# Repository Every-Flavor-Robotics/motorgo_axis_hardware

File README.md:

# MotorGo AXIS
## The aim of this project is to integrate a dual bldc motor controller with an ESP32 AND make it piHat compatible for the rpi 4 and 5
### Schematics and Layouts and Renders: 
(This is a first pass draft, so be patient with my formatting and content)

- Full board 3D:

- Top level

- Motor drivers 

- IMU 

- Power system 

- connectors 

- Dimensions 

## Demo
This is still in testing, but already at this state, it is capable of making 2 axis gantry robots quite easily.  Check out this project we made with it while developing the motor controller:
https://www.youtube.com/watch?v=p4cUWCG7fM4

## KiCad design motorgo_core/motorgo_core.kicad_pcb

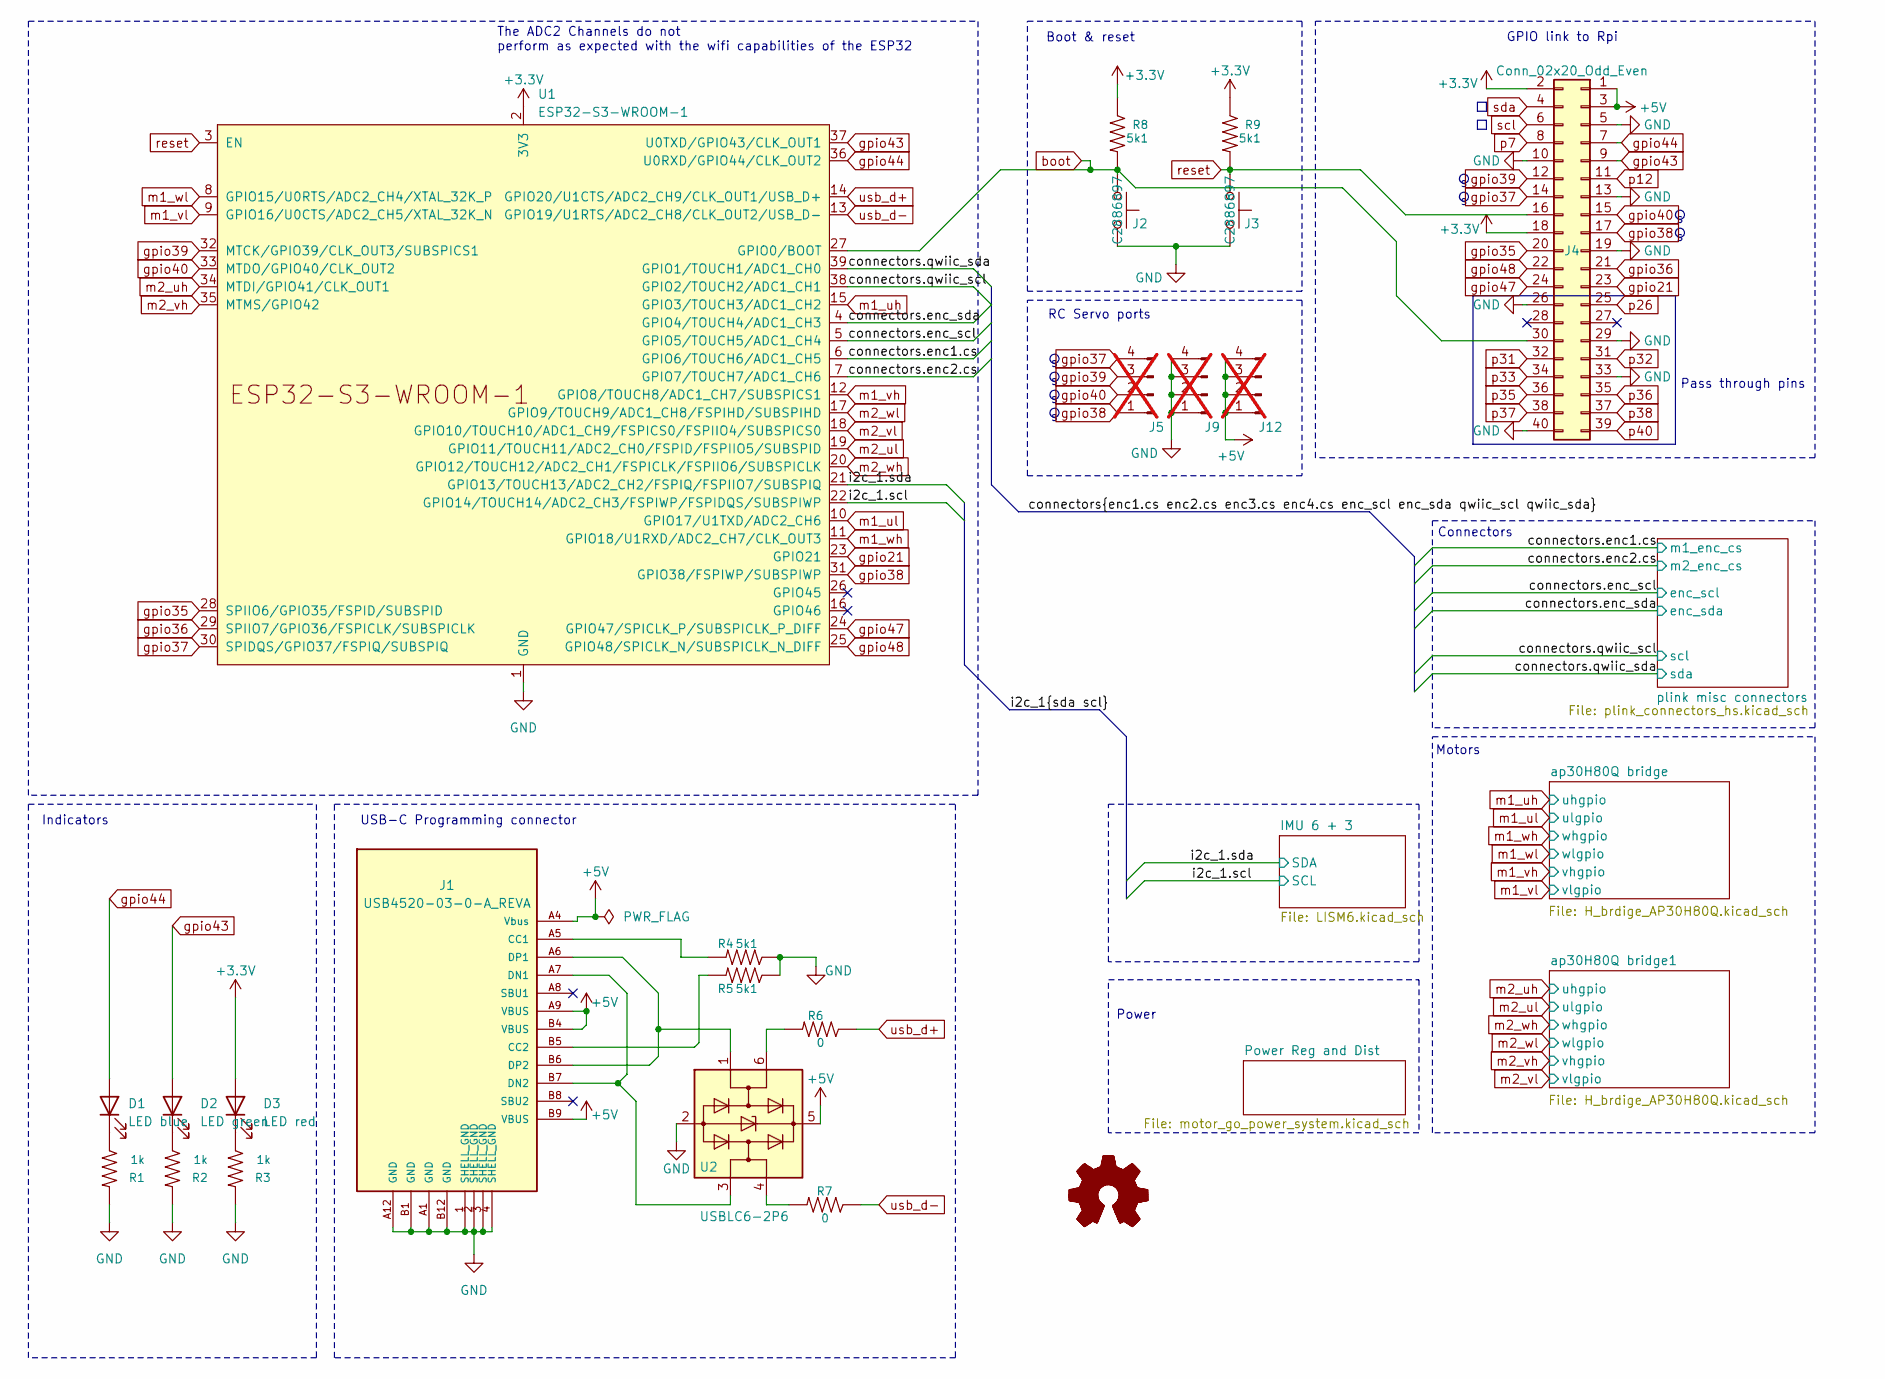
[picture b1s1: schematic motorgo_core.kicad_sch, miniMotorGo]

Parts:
D1: LED blue; LED_0805_2012Metric; LCSC_Part_Number C84259
D2: LED green; LED_0805_2012Metric; LCSC_Part_Number C84260
D3: LED red; LED_0805_2012Metric; LCSC_Part_Number C84256
J1: USB4520-03-0-A_REVA; USB-C-SMD_TYPEC-303-ACP16; LCSC_Part_Number C720628
J2, J3: C2886897; SW_SPST_TL3342; LCSC_Part_Number C2886897
J4: Conn_02x20_Odd_Even; PinSocket_2x20_P2.54mm_Vertical_SMD; LCSC_Part_Number C3975165
J5, J9, J12: Conn_01x04_Pin; PinHeader_1x04_P2.54mm_Vertical; not fitted
R1, R2, R3: 1k; R_0402_1005Metric; LCSC_Part_Number C11702
R4, R5, R8, R9: 5k1; R_0402_1005Metric; LCSC_Part_Number C25905
R6, R7: 0; R_0402_1005Metric; LCSC_Part_Number C3017451
U1: ESP32-S3-WROOM-1; LCSC_Part_Number C2913198
U2: USBLC6-2P6; SOT-666; LCSC_Part_Number C2827693

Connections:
+3.3V: D3.2 (A), J4.2, J4.18, R8.1, R9.1, U1.2 (3V3); also elsewhere on the board
+5V: J1.A4 (Vbus), J1.A9 (VBUS), J1.B4 (VBUS), J1.B9 (VBUS), J4.1, J4.3, J12.1, J12.2, J12.3, J12.4, U2.5 (VBUS); also elsewhere on the board
/connectors.enc1.cs: U1.6 (GPIO6/TOUCH6/ADC1_CH5); also elsewhere on the board
/connectors.enc2.cs: U1.7 (GPIO7/TOUCH7/ADC1_CH6); also elsewhere on the board
/connectors.enc_scl: U1.5 (GPIO5/TOUCH5/ADC1_CH4); also elsewhere on the board
/connectors.enc_sda: U1.4 (GPIO4/TOUCH4/ADC1_CH3); also elsewhere on the board
/i2c_1.scl: U1.22 (GPIO14/TOUCH14/ADC2_CH3/FSPIWP/FSPIDQS/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); also elsewhere on the board
/i2c_1.sda: U1.21 (GPIO13/TOUCH13/ADC2_CH2/FSPIQ/FSPIIO7/S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); also elsewhere on the board
GND: J1.1 (SHELL_GND), J1.2 (SHELL_GND), J1.3 (SHELL_GND), J1.4 (SHELL_GND), J1.A1 (GND), J1.A12 (GND), J1.B1 (GND), J1.B12 (GND), J2.1, J3.2, J4.5, J4.10, J4.13, J4.19, J4.26, J4.29, J4.33, J4.40, J9.1, J9.2, J9.3, J9.4, R1.2, R2.2, R3.2, R4.1, R5.1, U1.1 (GND), U1.40 (GND), U1.41 (GND), U2.2 (GND); also elsewhere on the board
unnamed: D1.1 (K), R1.1
unnamed: D2.1 (K), R2.1
unnamed: D3.1 (K), R3.1
unnamed: J1.A5 (CC1), R4.2
unnamed: J1.B5 (CC2), R5.2
unnamed: J1.A7 (DN1), J1.B7 (DN2), U2.3 (I/O2)
unnamed: J1.A6 (DP1), J1.B6 (DP2), U2.1 (I/O1)
unnamed: R6.2, U2.6 (I/O1)
unnamed: R7.2, U2.4 (I/O2)
boot: J2.2, J4.30, R8.2, U1.27 (GPIO0/BOOT); also elsewhere on the board
gpio21: J4.23, U1.23 (GPIO21); also elsewhere on the board
gpio35: J4.20, U1.28 (SPIIO6/GPIO35/FSPID/SUBSPID); also elsewhere on the board
gpio36: J4.21, U1.29 (SPIIO7/GPIO36/FSPICLK/SUBSPICLK); also elsewhere on the board
gpio37: J4.14, J5.4, U1.30 (SPIDQS/GPIO37/FSPIQ/SUBSPIQ); also elsewhere on the board
gpio38: J4.17, J5.1, U1.31 (GPIO38/FSPIWP/SUBSPIWP); also elsewhere on the board
gpio39: J4.12, J5.3, U1.32 (MTCK/GPIO39/CLK_OUT3/SUBSPICS1); also elsewhere on the board
gpio40: J4.15, J5.2, U1.33 (MTDO/GPIO40/CLK_OUT2); also elsewhere on the board
gpio43: D2.2 (A), J4.9, U1.37 (U0TXD/GPIO43/CLK_OUT1); also elsewhere on the board
gpio44: D1.2 (A), J4.7, U1.36 (U0RXD/GPIO44/CLK_OUT2); also elsewhere on the board
gpio47: J4.24, U1.24 (GPIO47/SPICLK_P/SUBSPICLK_P_DIFF); also elsewhere on the board
gpio48: J4.22, U1.25 (GPIO48/SPICLK_N/SUBSPICLK_N_DIFF); also elsewhere on the board
m1_uh: U1.15 (GPIO3/TOUCH3/ADC1_CH2); also elsewhere on the board
m1_ul: U1.10 (GPIO17/U1TXD/ADC2_CH6); also elsewhere on the board
m1_vh: U1.12 (GPIO8/TOUCH8/ADC1_CH7/SUBSPICS1); also elsewhere on the board
m1_vl: U1.9 (GPIO16/U0CTS/ADC2_CH5/XTAL_32K_N); also elsewhere on the board
m1_wh: U1.11 (GPIO18/U1RXD/ADC2_CH7/CLK_OUT3); also elsewhere on the board
m1_wl: U1.8 (GPIO15/U0RTS/ADC2_CH4/XTAL_32K_P); also elsewhere on the board
m2_uh: U1.34 (MTDI/GPIO41/CLK_OUT1); also elsewhere on the board
m2_ul: U1.19 (GPIO11/TOUCH11/ADC2_CH0/FSPID/FSPIIO5/S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); also elsewhere on the board
m2_vh: U1.35 (MTMS/GPIO42); also elsewhere on the board
m2_vl: U1.18 (GPIO10/TOUCH10/ADC1_CH9/FSPICS0/FSPIIO4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); also elsewhere on the board
m2_wh: U1.20 (GPIO12/TOUCH12/ADC2_CH1/FSPICLK/FSPIIO6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); also elsewhere on the board
m2_wl: U1.17 (GPIO9/TOUCH9/ADC1_CH8/FSPIHD/SUBSPIHD); also elsewhere on the board
p7: J4.8; also elsewhere on the board
p12: J4.11; also elsewhere on the board
p26: J4.25; also elsewhere on the board
p31: J4.32; also elsewhere on the board
p32: J4.31; also elsewhere on the board
p33: J4.34; also elsewhere on the board
p35: J4.36; also elsewhere on the board
p36: J4.35; also elsewhere on the board
p37: J4.38; also elsewhere on the board
p38: J4.37; also elsewhere on the board
p40: J4.39; also elsewhere on the board
reset: J3.1, J4.16, R9.2, U1.3 (EN); also elsewhere on the board
scl: J4.6, U1.38 (GPIO2/TOUCH2/ADC1_CH1); also elsewhere on the board
sda: J4.4, U1.39 (GPIO1/TOUCH1/ADC1_CH0); also elsewhere on the board
usb_d+: R6.1, U1.14 (GPIO20/U1CTS/ADC2_CH9/CLK_OUT1/USB_D+)
usb_d-: R7.1, U1.13 (GPIO19/U1RTS/ADC2_CH8/CLK_OUT2/USB_D-)

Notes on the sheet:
USB-C Programming connector
Motors
Power
Boot & reset
Indicators
The ADC2 Channels do not perform as expected with the wifi capabilities of the ESP32
Pass through pins
Connectors
RC Servo ports
GPIO link to Rpi

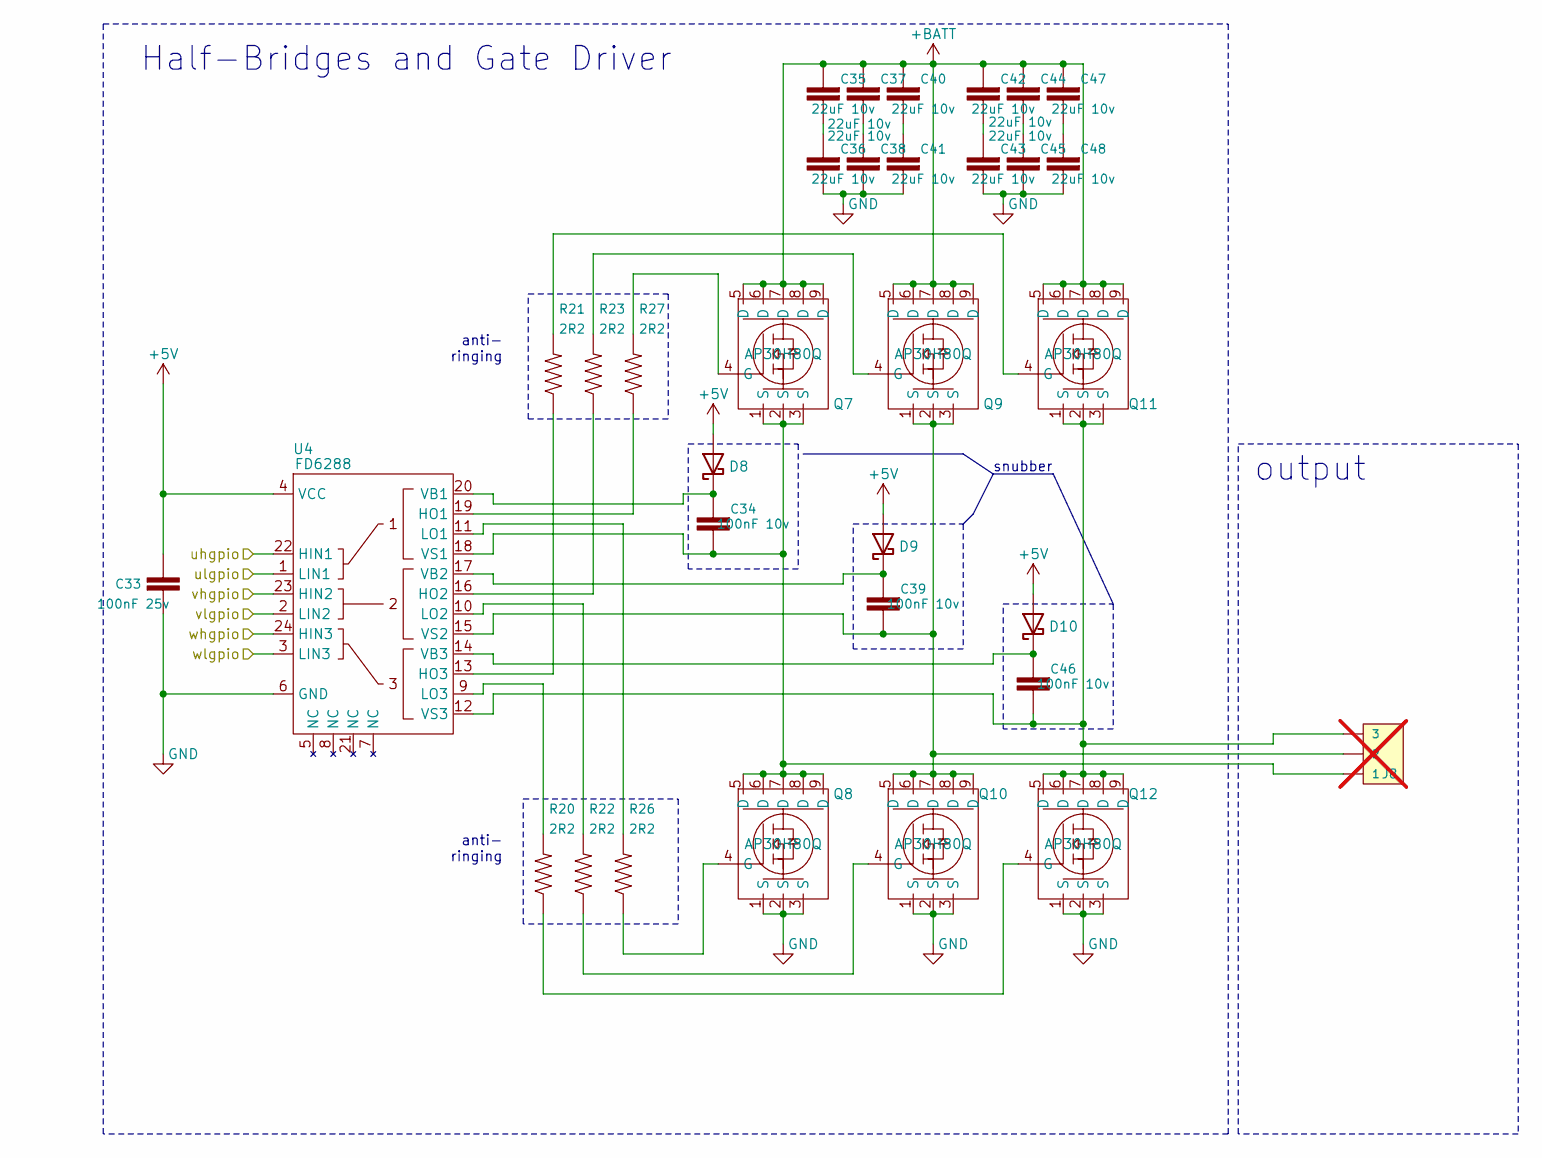
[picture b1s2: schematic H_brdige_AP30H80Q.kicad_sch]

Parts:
C33: 100nF 25v; C_0201_0603Metric; Manufacturer_Part_Number CC0402KRX7R7BB104; LCSC_Part_Number C60474
C34, C39, C46: 100nF 10v; C_0201_0603Metric; Manufacturer_Part_Number CC0402KRX7R7BB104; LCSC_Part_Number C60474
C35, C36, C37, C38, C40, C41, C42, C43, C44, C45, C47, C48: 22uF 10v; C_0402_1005Metric; LCSC_Part_Number C3845593
D8, D9, D10: D_Schottky C7420331; B5819WS_SOD-323; LCSC_Part_Number C7420331
J8: DNP; 3 phase motor; not fitted
Q7, Q8, Q9, Q10, Q11, Q12: AP30H80Q; AP30H80Q_DFN-8; LCSC_Part_Number C2828592
R20, R21, R22, R23, R26, R27: 2R2; R_0402_1005Metric; LCSC_Part_Number C25158
U4: FD6288; FD6288Q_QFN-24; LCSC_Part_Number C328453

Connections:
+5V: C33.1, D8.2 (A), D9.2 (A), D10.2 (A), U4.4 (VCC); also elsewhere on the board
+BATT: C35.2, C37.2, C40.2, C42.2, C44.2, C47.2, Q7.5 (D), Q7.6 (D), Q7.7 (D), Q7.8 (D), Q7.9 (D), Q9.5 (D), Q9.6 (D), Q9.7 (D), Q9.8 (D), Q9.9 (D), Q11.5 (D), Q11.6 (D), Q11.7 (D), Q11.8 (D), Q11.9 (D); also elsewhere on the board
GND: C33.2, C36.1, C38.1, C41.1, C43.1, C45.1, C48.1, Q8.1 (S), Q8.2 (S), Q8.3 (S), Q10.1 (S), Q10.2 (S), Q10.3 (S), Q12.1 (S), Q12.2 (S), Q12.3 (S), U4.6 (GND); also elsewhere on the board
unnamed: C35.1, C36.2
unnamed: C37.1, C38.2
unnamed: C40.1, C41.2
unnamed: C42.1, C43.2
unnamed: C44.1, C45.2
unnamed: C47.1, C48.2
unnamed: C34.2, D8.1 (K), U4.20 (VB1)
unnamed: C39.2, D9.1 (K), U4.17 (VB2)
unnamed: C46.2, D10.1 (K), U4.14 (VB3)
unnamed: Q7.4 (G), R27.2
unnamed: Q8.4 (G), R26.1
unnamed: Q9.4 (G), R23.2
unnamed: Q10.4 (G), R22.1
unnamed: Q11.4 (G), R21.2
unnamed: Q12.4 (G), R20.1
unnamed: R27.1, U4.19 (HO1)
unnamed: R23.1, U4.16 (HO2)
unnamed: R21.1, U4.13 (HO3)
unnamed: R26.2, U4.11 (LO1)
unnamed: R22.2, U4.10 (LO2)
unnamed: R20.2, U4.9 (LO3)
unnamed: C34.1, J8.1, Q7.1 (S), Q7.2 (S), Q7.3 (S), Q8.5 (D), Q8.6 (D), Q8.7 (D), Q8.8 (D), Q8.9 (D), U4.18 (VS1)
unnamed: C39.1, J8.2, Q9.1 (S), Q9.2 (S), Q9.3 (S), Q10.5 (D), Q10.6 (D), Q10.7 (D), Q10.8 (D), Q10.9 (D), U4.15 (VS2)
unnamed: C46.1, J8.3, Q11.1 (S), Q11.2 (S), Q11.3 (S), Q12.5 (D), Q12.6 (D), Q12.7 (D), Q12.8 (D), Q12.9 (D), U4.12 (VS3)
m2_uh: U4.22 (HIN1); also elsewhere on the board
m2_ul: U4.1 (LIN1); also elsewhere on the board
m2_vh: U4.23 (HIN2); also elsewhere on the board
m2_vl: U4.2 (LIN2); also elsewhere on the board
m2_wh: U4.24 (HIN3); also elsewhere on the board
m2_wl: U4.3 (LIN3); also elsewhere on the board

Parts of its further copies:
C3: 100nF 25v; C_0201_0603Metric; Manufacturer_Part_Number CC0402KRX7R7BB104; LCSC_Part_Number C60474
C4, C9, C26: 100nF 10v; C_0201_0603Metric; Manufacturer_Part_Number CC0402KRX7R7BB104; LCSC_Part_Number C60474
C5, C6, C7, C8, C10, C11, C12, C13, C14, C21, C27, C28: 22uF 10v; C_0402_1005Metric; LCSC_Part_Number C3845593
D5, D6, D7: D_Schottky C7420331; B5819WS_SOD-323; LCSC_Part_Number C7420331
J6: DNP; 3 phase motor; not fitted
Q1, Q2, Q3, Q4, Q5, Q6: AP30H80Q; AP30H80Q_DFN-8; LCSC_Part_Number C2828592
R10, R11, R12, R13, R14, R15: 2R2; R_0402_1005Metric; LCSC_Part_Number C25158
U3: FD6288; FD6288Q_QFN-24; LCSC_Part_Number C328453

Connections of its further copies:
+5V: C3.1, D5.2 (A), D6.2 (A), D7.2 (A), U3.4 (VCC); also elsewhere on the board
+BATT: C5.2, C7.2, C10.2, C12.2, C14.2, C27.2, Q1.5 (D), Q1.6 (D), Q1.7 (D), Q1.8 (D), Q1.9 (D), Q3.5 (D), Q3.6 (D), Q3.7 (D), Q3.8 (D), Q3.9 (D), Q5.5 (D), Q5.6 (D), Q5.7 (D), Q5.8 (D), Q5.9 (D); also elsewhere on the board
GND: C3.2, C6.1, C8.1, C11.1, C13.1, C21.1, C28.1, Q2.1 (S), Q2.2 (S), Q2.3 (S), Q4.1 (S), Q4.2 (S), Q4.3 (S), Q6.1 (S), Q6.2 (S), Q6.3 (S), U3.6 (GND); also elsewhere on the board
unnamed: C5.1, C6.2
unnamed: C7.1, C8.2
unnamed: C10.1, C11.2
unnamed: C12.1, C13.2
unnamed: C14.1, C21.2
unnamed: C27.1, C28.2
unnamed: C4.2, D5.1 (K), U3.20 (VB1)
unnamed: C9.2, D6.1 (K), U3.17 (VB2)
unnamed: C26.2, D7.1 (K), U3.14 (VB3)
unnamed: Q1.4 (G), R15.2
unnamed: Q2.4 (G), R14.1
unnamed: Q3.4 (G), R13.2
unnamed: Q4.4 (G), R12.1
unnamed: Q5.4 (G), R11.2
unnamed: Q6.4 (G), R10.1
unnamed: R15.1, U3.19 (HO1)
unnamed: R13.1, U3.16 (HO2)
unnamed: R11.1, U3.13 (HO3)
unnamed: R14.2, U3.11 (LO1)
unnamed: R12.2, U3.10 (LO2)
unnamed: R10.2, U3.9 (LO3)
unnamed: C4.1, J6.1, Q1.1 (S), Q1.2 (S), Q1.3 (S), Q2.5 (D), Q2.6 (D), Q2.7 (D), Q2.8 (D), Q2.9 (D), U3.18 (VS1)
unnamed: C9.1, J6.2, Q3.1 (S), Q3.2 (S), Q3.3 (S), Q4.5 (D), Q4.6 (D), Q4.7 (D), Q4.8 (D), Q4.9 (D), U3.15 (VS2)
unnamed: C26.1, J6.3, Q5.1 (S), Q5.2 (S), Q5.3 (S), Q6.5 (D), Q6.6 (D), Q6.7 (D), Q6.8 (D), Q6.9 (D), U3.12 (VS3)
m1_uh: U3.22 (HIN1); also elsewhere on the board
m1_ul: U3.1 (LIN1); also elsewhere on the board
m1_vh: U3.23 (HIN2); also elsewhere on the board
m1_vl: U3.2 (LIN2); also elsewhere on the board
m1_wh: U3.24 (HIN3); also elsewhere on the board
m1_wl: U3.3 (LIN3); also elsewhere on the board

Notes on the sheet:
output
anti- ringing
Half-Bridges and Gate Driver
snubber

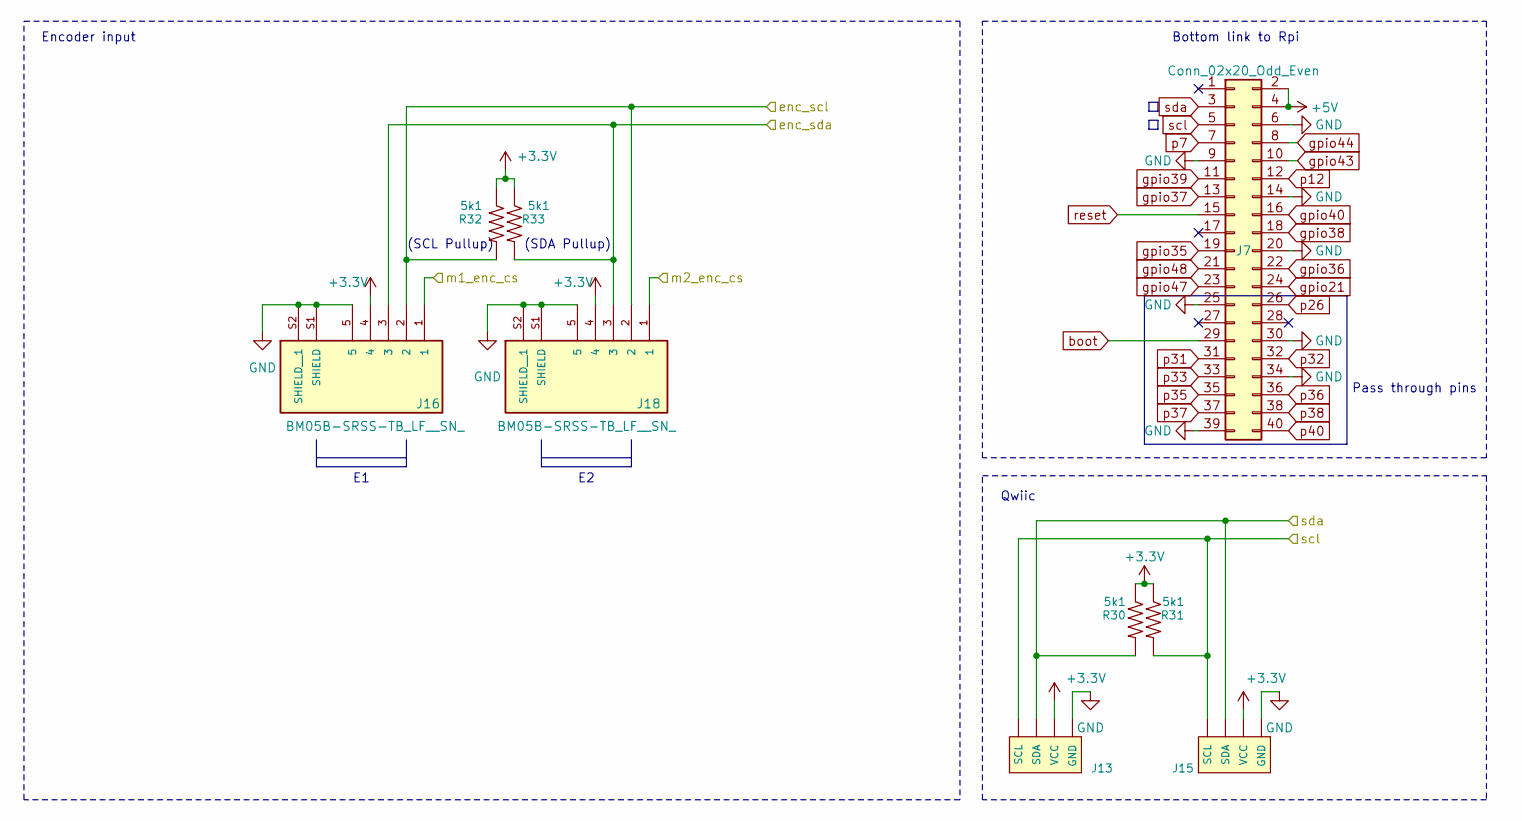
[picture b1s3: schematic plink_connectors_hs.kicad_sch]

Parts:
J7: Conn_02x20_Odd_Even; PinSocket_2x20_P2.54mm_Vertical_SMD; LCSC_Part_Number C3975165
J13, J15: I2C_STANDARDQWIIC; JST_SH_BM04B-SRSS-TB_1x04-1MP_P1.00mm_Vertical; LCSC_Part_Number C160404
J16, J18: BM05B-SRSS-TB_LF__SN_; JST_SH_BM05B-SRSS-TB_1x05-1MP_P1.00mm_Vertical; PARTREV N/A; LCSC_Part_Number C265092
R30, R31, R32, R33: 5k1; R_0402_1005Metric; LCSC_Part_Number C25905

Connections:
+3.3V: J13.2 (VCC), J15.2 (VCC), J16.4, J18.4, R30.1, R31.1, R32.1, R33.1; also elsewhere on the board
+5V: J7.2, J7.4; also elsewhere on the board
/connectors.enc1.cs: J16.1; also elsewhere on the board
/connectors.enc2.cs: J18.1; also elsewhere on the board
/connectors.enc_scl: J16.2, J18.2, R32.2; also elsewhere on the board
/connectors.enc_sda: J16.3, J18.3, R33.2; also elsewhere on the board
GND: J7.6, J7.9, J7.14, J7.20, J7.25, J7.30, J7.34, J7.39, J13.1 (GND), J15.1 (GND), J16.5, J16.S1 (SHIELD), J16.S2 (SHIELD__1), J18.5, J18.S1 (SHIELD), J18.S2 (SHIELD__1); also elsewhere on the board
boot: J7.29; also elsewhere on the board
gpio21: J7.24; also elsewhere on the board
gpio35: J7.19; also elsewhere on the board
gpio36: J7.22; also elsewhere on the board
gpio37: J7.13; also elsewhere on the board
gpio38: J7.18; also elsewhere on the board
gpio39: J7.11; also elsewhere on the board
gpio40: J7.16; also elsewhere on the board
gpio43: J7.10; also elsewhere on the board
gpio44: J7.8; also elsewhere on the board
gpio47: J7.23; also elsewhere on the board
gpio48: J7.21; also elsewhere on the board
p7: J7.7; also elsewhere on the board
p12: J7.12; also elsewhere on the board
p26: J7.26; also elsewhere on the board
p31: J7.31; also elsewhere on the board
p32: J7.32; also elsewhere on the board
p33: J7.33; also elsewhere on the board
p35: J7.35; also elsewhere on the board
p36: J7.36; also elsewhere on the board
p37: J7.37; also elsewhere on the board
p38: J7.38; also elsewhere on the board
p40: J7.40; also elsewhere on the board
reset: J7.15; also elsewhere on the board
scl: J7.5, J13.4 (SCL), J15.4 (SCL), R31.2; also elsewhere on the board
sda: J7.3, J13.3 (SDA), J15.3 (SDA), R30.2; also elsewhere on the board

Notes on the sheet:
Qwiic
Bottom link to Rpi
Encoder input
(SCL Pullup)
Pass through pins
(SDA Pullup)

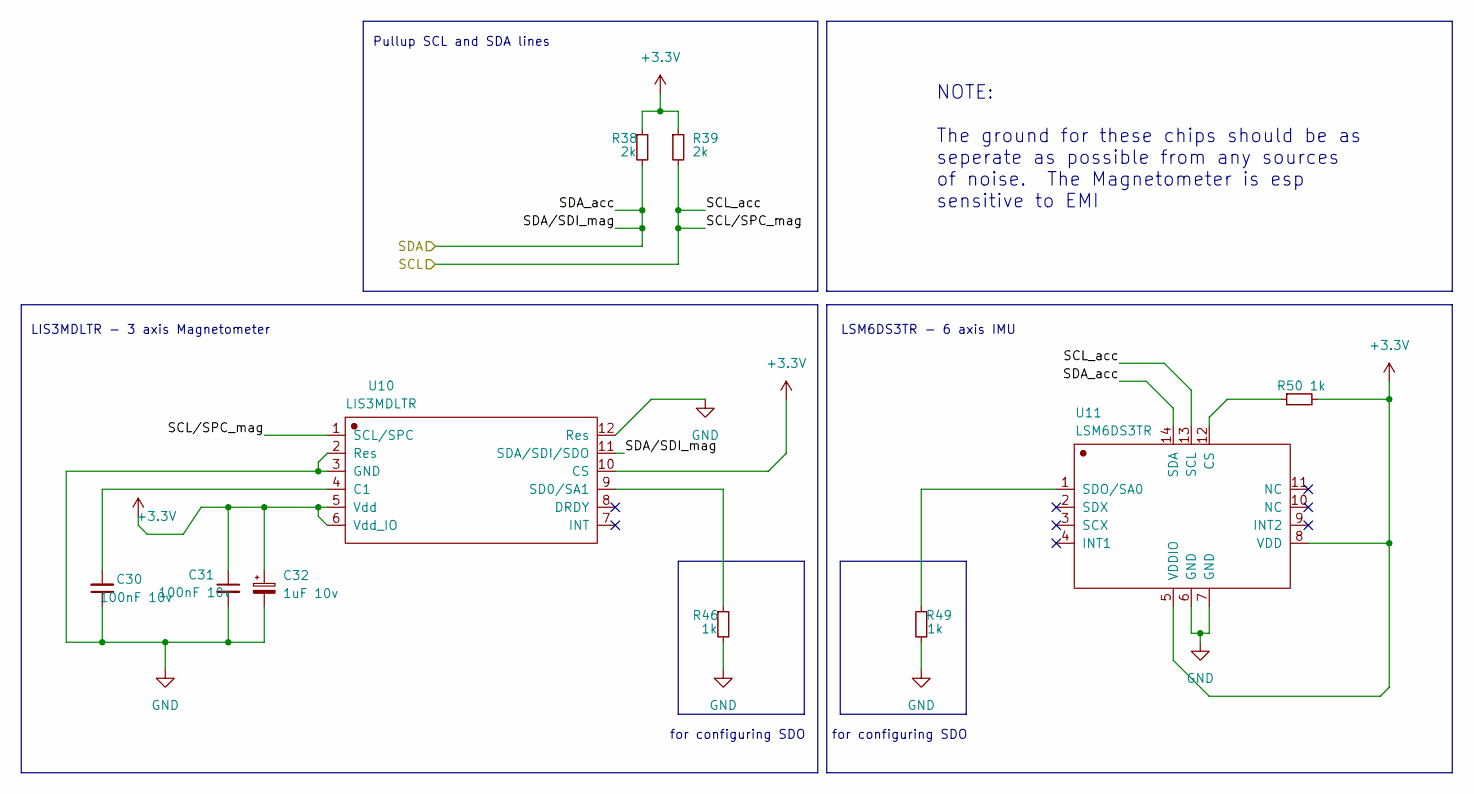
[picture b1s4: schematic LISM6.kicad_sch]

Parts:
C30, C31: 100nF 10v; C_0201_0603Metric; LCSC_Part_Number C880603
C32: 1uF 10v; C_0603_1608Metric; LCSC_Part_Number C15849
R38, R39: 2k; R_0402_1005Metric; LCSC_Part_Number C4109
R46, R49, R50: 1k; R_0402_1005Metric; LCSC_Part_Number C11702
U10: LIS3MDLTR; LIS3MDLTR_LGA-12; LCSC_Part_Number C478483
U11: LSM6DS3TR; LSM6DSOTR_LGA-14; LCSC_Part_Number C95230

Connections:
+3.3V: C31.1, C32.1, R38.1, R39.1, R50.2, U10.5 (Vdd), U10.6 (Vdd_IO), U10.10 (CS), U11.5 (VDDIO), U11.8 (VDD); also elsewhere on the board
/i2c_1.scl: R39.2, U10.1 (SCL/SPC), U11.13 (SCL); also elsewhere on the board
/i2c_1.sda: R38.2, U10.11 (SDA/SDI/SDO), U11.14 (SDA); also elsewhere on the board
GND: C30.1, C31.2, C32.2, R46.2, R49.2, U10.2 (Res), U10.3 (GND), U10.12 (Res), U11.6 (GND), U11.7 (GND); also elsewhere on the board
unnamed: C30.2, U10.4 (C1)
unnamed: R46.1, U10.9 (SD0/SA1)
unnamed: R50.1, U11.12 (CS)
unnamed: R49.1, U11.1 (SDO/SA0)

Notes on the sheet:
NOTE: The ground for these chips should be as seperate as possible from any sources of noise. The Magnetometer is esp sensitive to EMI
for configuring SDO
LSM6DS3TR - 6 axis IMU
Pullup SCL and SDA lines
LIS3MDLTR - 3 axis Magnetometer

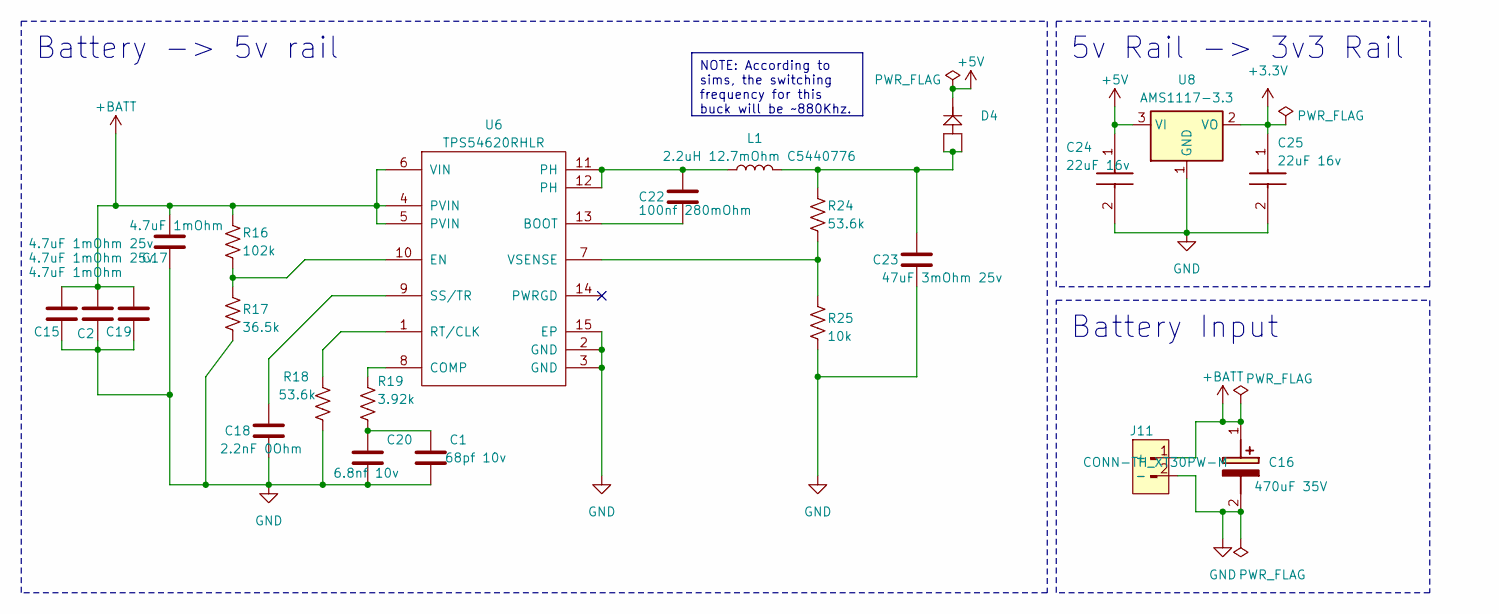
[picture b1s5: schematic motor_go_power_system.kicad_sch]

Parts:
C1: 68pf 10v; C_0201_0603Metric; LCSC_Part_Number C3037638
C2, C15: 4.7uF 1mOhm 25v; C_0805_2012Metric; LCSC_Part_Number C5448891
C16: 470uF 35V; CP_Elec_10x10.5; Mouser Part Number 140-RGA221M1EBK0811G
C17: 4.7uF 1mOhm; C_0603_1608Metric; LCSC_Part_Number C6119856
C18: 2.2nF 0Ohm; C_0201_0603Metric; LCSC_Part_Number C285033
C19: 4.7uF 1mOhm; C_0805_2012Metric; LCSC_Part_Number C5448891
C20: 6.8nf 10v; C_0201_0603Metric; LCSC_Part_Number C3037638
C22: 100nf 280mOhm; C_0402_1005Metric; LCSC_Part_Number C880603
C23: 47uF 3mOhm 25v; C_1210_3225Metric; LCSC_Part_Number C7432791
C24, C25: 22uF 16v; C_0603_1608Metric; Mouser Part Number 187-CL21A226MQQNNNE
D4: Schottky_SB1045L_C908747; TO-277_3P-L5.4-W4.0-LS6.5-TR
J11: CONN-TH_XT30PW-M; LCSC_Part_Number C319099
L1: 2.2uH 12.7mOhm C5440776; IND-SMD_L6.6-W6.4_CKSTT0610; LCSC_Part_Number C5440776
R16: 102k; R_0402_1005Metric; LCSC_Part_Number C2933066
R17: 36.5k; R_0402_1005Metric; LCSC_Part_Number C25887
R18: 53.6k; R_0402_1005Metric; LCSC_Part_Number C5153961
R19: 3.92k; R_0402_1005Metric; LCSC_Part_Number C3013164
R24: 53.6k; R_0402_1005Metric; LCSC_Part_Number C2998086
R25: 10k; R_0402_1005Metric; LCSC_Part_Number C2906885
U6: TPS54620RHLR; VQFN-14_L3.5-W3.5-P0.50-TL-EP_TPS54622RHLT; LCSC_Part_Number C263274
U8: AMS1117-3.3; SOT-223-3_TabPin2; LCSC_Part_Number C347222

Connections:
+3.3V: C25.1, U8.2 (VO); also elsewhere on the board
+5V: C24.1, D4.2 (K), U8.3 (VI); also elsewhere on the board
+BATT: C2.1, C15.1, C16.1 (+), C17.1, C19.1, J11.1 (+), R16.1, U6.4 (PVIN), U6.5 (PVIN), U6.6 (VIN); also elsewhere on the board
GND: C1.2, C2.2, C15.2, C16.2 (-), C17.2, C18.2, C19.2, C20.2, C23.2, C24.2, C25.2, J11.2 (-), J11.3, J11.4, R17.2, R18.2, R25.2, U6.2 (GND), U6.3 (GND), U6.15 (EP), U8.1 (GND); also elsewhere on the board
unnamed: C1.1, C20.1, R19.2
unnamed: C22.1, L1.1, U6.11 (PH), U6.12 (PH)
unnamed: C23.1, D4.1 (A), D4.3 (A), L1.2, R24.1
unnamed: C22.2, U6.13 (BOOT)
unnamed: R19.1, U6.8 (COMP)
unnamed: R16.2, R17.1, U6.10 (EN)
unnamed: R18.1, U6.1 (RT/CLK)
unnamed: C18.1, U6.9 (SS/TR)
unnamed: R24.2, R25.1, U6.7 (VSENSE)

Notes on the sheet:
NOTE: According to sims, the switching frequency for this buck will be ~880Khz.
Battery -> 5v rail
Battery Input
5v Rail -> 3v3 Rail

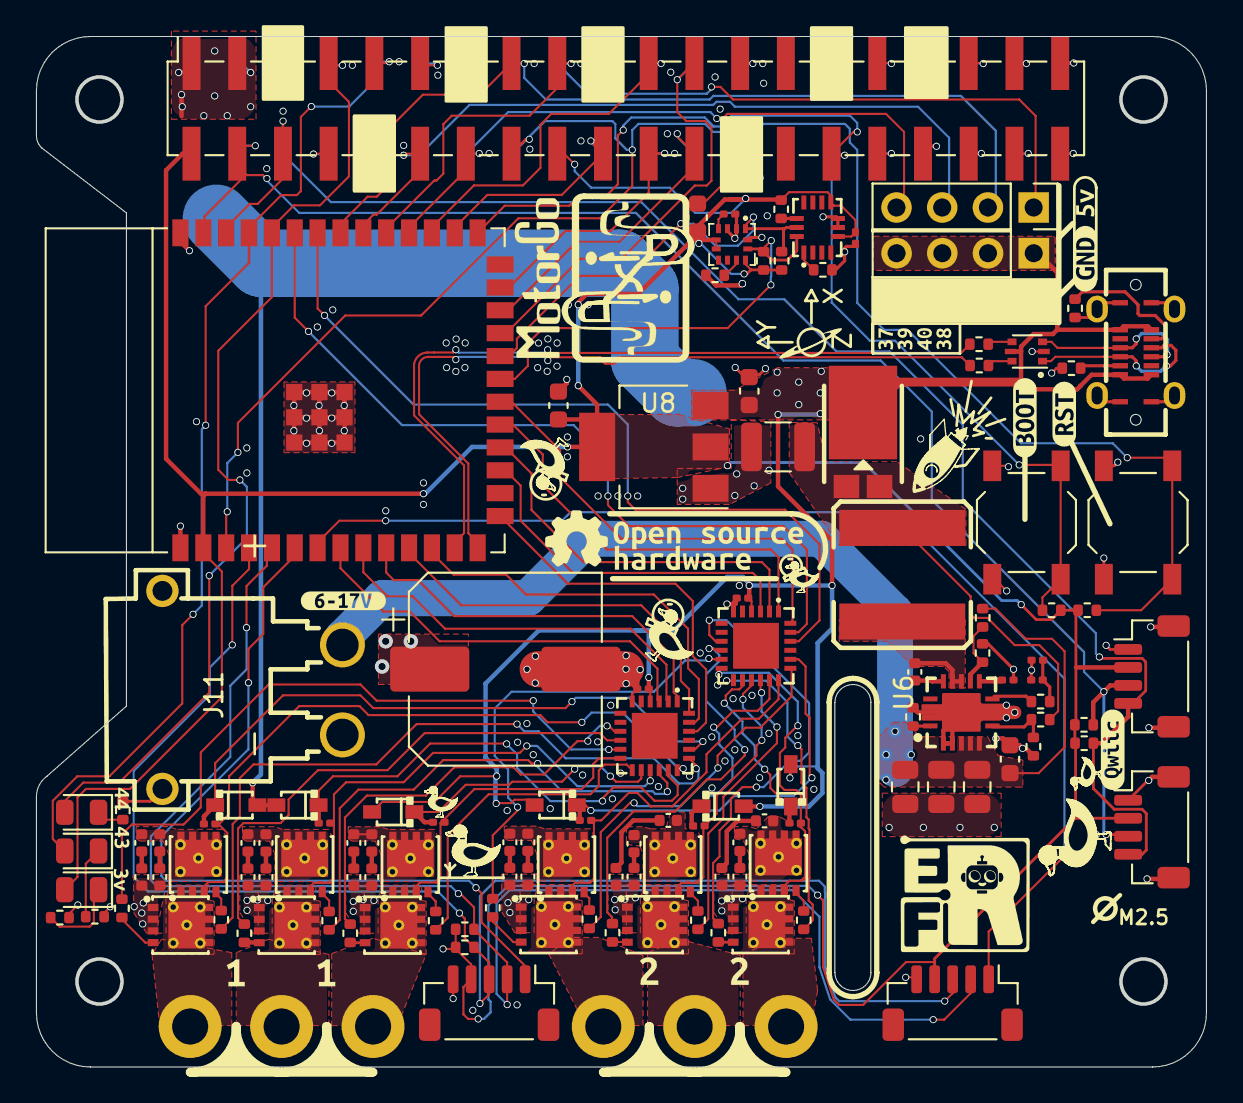
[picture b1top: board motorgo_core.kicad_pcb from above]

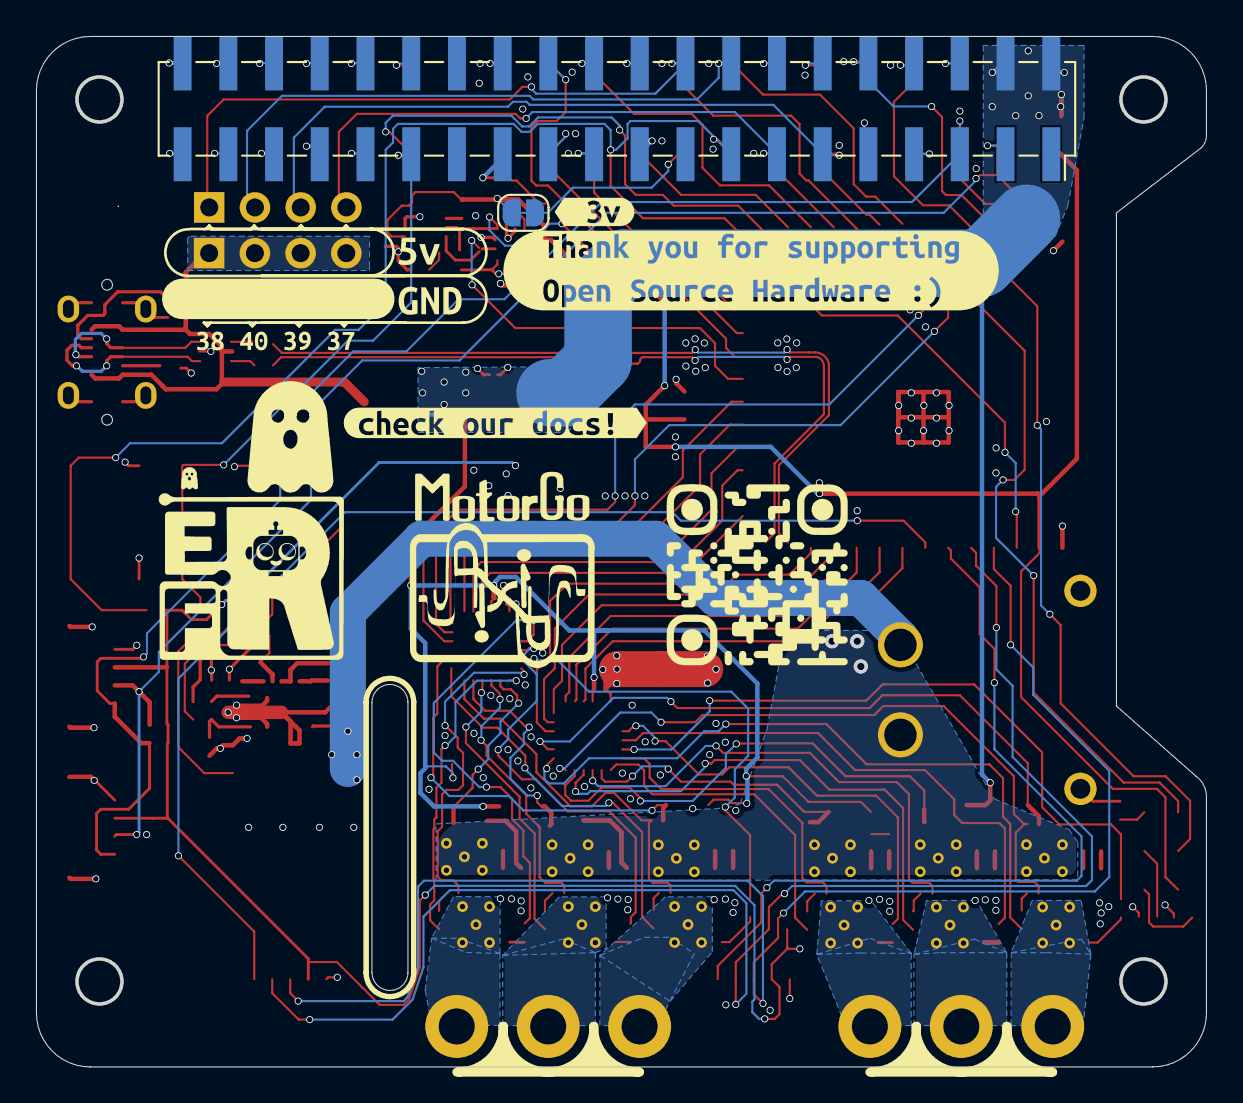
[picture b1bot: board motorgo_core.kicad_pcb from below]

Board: 4 copper layers, 65.0 x 57.2 mm, 150 parts (7 on the bottom side), 120 nets.

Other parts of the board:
kibuzzard-67A57D3F: G***; kibuzzard-67A57D3F
kibuzzard-670FEBB5: G***; kibuzzard-670FEBB5
kibuzzard-6740A48B: G***; kibuzzard-6740A48B
kibuzzard-6740A353: G***; kibuzzard-6740A353
kibuzzard-6740A543: G***; kibuzzard-6740A543
kibuzzard-6740A668, kibuzzard-6740A668#2: G***; kibuzzard-6740A668
kibuzzard-6740A681, kibuzzard-6740A681#2: G***; kibuzzard-6740A681
kibuzzard-6740AFFF: G***; kibuzzard-6740AFFF
kibuzzard-6740B00B: G***; kibuzzard-6740B00B
kibuzzard-6740B0CA: G***; kibuzzard-6740B0CA
kibuzzard-6740B1FD: G***; kibuzzard-6740B1FD
kibuzzard-6740B03C: G***; kibuzzard-6740B03C
kibuzzard-6740B20C: G***; kibuzzard-6740B20C
kibuzzard-6740E9DD: G***; kibuzzard-6740E9DD
kibuzzard-6740EACA: G***; kibuzzard-6740EACA
kibuzzard-67324B8C: G***; kibuzzard-67324B8C
kibuzzard-67324B68: G***; kibuzzard-67324B68
kibuzzard-67324B83: G***; kibuzzard-67324B83
kibuzzard-673237E1: G***; kibuzzard-673237E1

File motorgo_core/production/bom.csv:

Designator,Footprint,Quantity,Value,LCSC Part #
C1,0201,1,68pf 10v,
"C10, C11, C12, C13, C14, C21, C27, C28, C35, C36, C37, C38, C40, C41, C42, C43, C44, C45, C47, C48, C5, C6, C7, C8",0402,24,22uF 10v,
"C15, C2",0805,2,4.7uF 1mOhm 25v,
C16,CP_Elec_10x10.5,1,470uF 35V,
C17,0603,1,4.7uF 1mOhm,
C18,0201,1,2.2nF 0Ohm,
C19,0805,1,4.7uF 1mOhm,
C20,0201,1,6.8nf 10v,
C22,0402,1,100nf 280mOhm,
C23,1210,1,47uF 3mOhm 25v,
"C24, C25",0603,2,22uF 16v,
"C26, C30, C31, C34, C39, C4, C46, C9",0201,8,100nF 10v,
"C3, C33",0201,2,100nF 25v,
C32,0603,1,1uF 10v,
D1,0805,1,LED blue,
"D10, D5, D6, D7, D8, D9",B5819WS_SOD-323,6,D_Schottky C7420331,
D2,0805,1,LED green,
D3,0805,1,LED red,
D4,TO-277_3P-L5.4-W4.0-LS6.5-TR,1,Schottky_SB1045L_C908747,
J1,USB-C-SMD_TYPEC-303-ACP16,1,USB4520-03-0-A_REVA,
J11,CONN-TH_XT30PW-M,1,xt30,
"J12, J5, J9",PinHeader_1x04_P2.54mm_Vertical,3,Conn_01x04_Pin,
"J13, J15",JST_SH_BM04B-SRSS-TB_1x04-1MP_P1.00mm_Vertical,2,I2C_STANDARDQWIIC,
"J16, J18",JST_SH_BM05B-SRSS-TB_1x05-1MP_P1.00mm_Vertical,2,BM05B-SRSS-TB_LF__SN_,
"J2, J3",SW_SPST_TL3342,2,C2886897,
"J4, J7",PinSocket_2x20_P2.54mm_Vertical_SMD,2,Conn_02x20_Odd_Even,
"J6, J8",3 phase motor,2,DNP,
L1,IND-SMD_L6.6-W6.4_CKSTT0610,1,2.2uH 12.7mOhm C5440776,
"Q1, Q10, Q11, Q12, Q2, Q3, Q4, Q5, Q6, Q7, Q8, Q9",AP30H80Q_DFN-8,12,AP30H80Q,
"R1, R2, R3, R46, R49, R50",0402,6,1k,
"R10, R11, R12, R13, R14, R15, R20, R21, R22, R23, R26, R27",0402,12,2R2,
R16,0402,1,102k,
R17,0402,1,36.5k,
"R18, R24",0402,2,53.6k,
R19,0402,1,3.92k,
R25,0402,1,10k,
"R30, R31, R32, R33, R4, R5, R8, R9",0402,8,5k1,
"R38, R39",0402,2,2k,
"R6, R7",0402,2,0,
U1,ESP32-S3-WROOM-1,1,ESP32-S3-WROOM-1,
U10,LIS3MDLTR_LGA-12,1,LIS3MDLTR,
U11,LSM6DSOTR_LGA-14,1,LSM6DS3TR,
U2,SOT-666,1,USBLC6-2P6,
"U3, U4",FD6288Q_QFN-24,2,FD6288,
U6,VQFN-14_L3.5-W3.5-P0.50-TL-EP_TPS54622RHLT,1,TPS54620RHLR,
U8,SOT-223-3_TabPin2,1,AMS1117-3.3,

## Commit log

2024-11-14 initial board design copper layers and components
2025-01-04 update to recent production
2025-02-07 fix polarity of our xt30 connector, add jumper to disconnect 3v rail from pi-header
2025-02-08 add 3d STEP file of Axis Board
2026-04-27 removed a lot of bloat from the repo - aggressive removal
